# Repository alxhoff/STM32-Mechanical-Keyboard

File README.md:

# HID Keyboard - rebooted, stay tuned

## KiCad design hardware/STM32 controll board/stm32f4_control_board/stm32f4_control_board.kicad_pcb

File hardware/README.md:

# mech-keyboard-hardware
Hardware to accompany the stm32 firmware. Test board is based around a Nucleo144

## Status

Test keypads have been fabricated and tested working, test keyboard is in final stages of design.

## Images

https://photos.app.goo.gl/a2BMehDUMZQ9xBT23
https://photos.app.goo.gl/sn7a3JNhBGbZmrqK2

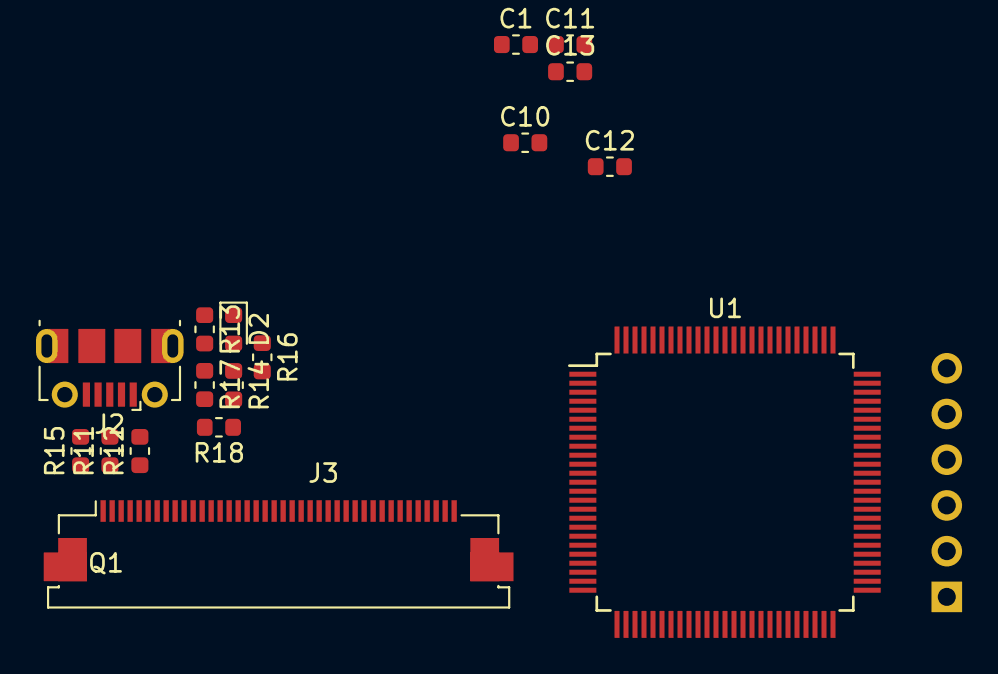
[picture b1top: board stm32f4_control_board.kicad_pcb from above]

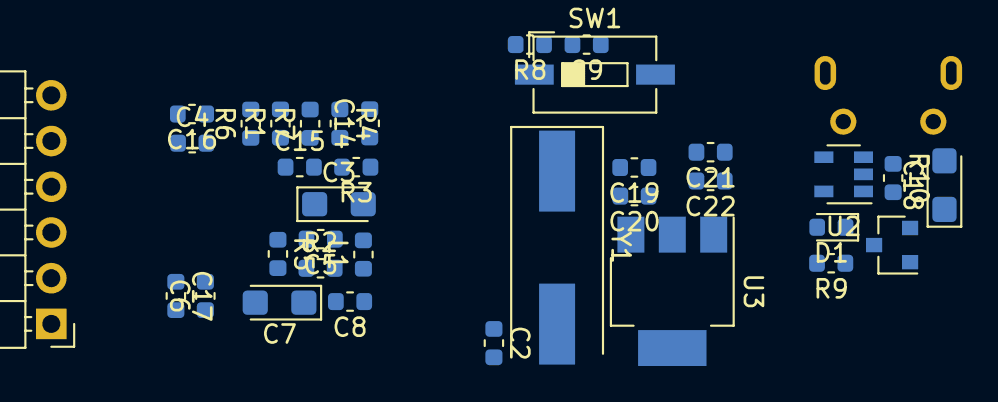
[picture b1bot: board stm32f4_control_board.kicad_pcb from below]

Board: 2 copper layers, 52 parts (35 on the bottom side), 54 nets, no tracks yet.

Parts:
C1, C2: 20pF; C_0603_1608Metric
C3, C7, C18: 1uF; CP_EIA-3216-18_Kemet-A
C4, C6: 2.2uF; C_0603_1608Metric
C5, C8, C9, C10, C11, C12, C13, C14, C15, C16, C17, C20, C22: 100nF; C_0603_1608Metric
C19, C21: 1uF; C_0603_1608Metric
D1: Green; D_0603_1608Metric
D2: Red; D_0603_1608Metric
J1: Conn_01x06_Female; PinHeader_1x06_P2.54mm_Horizontal
J2: USB_B_Micro; USB_Micro-B_Molex-105017-0001
J3: Conn_01x26_Female; Molex_54132-5033_1x40-1MP_P0.5mm_Horizontal
L1: L_Small; L_0603_1608Metric
Q1: 9013; SOT-23
R1: 510; R_0603_1608Metric
R2: 47; R_0603_1608Metric
R3, R4, R15, R17: 0; R_0603_1608Metric
R5, R8, R18: 10K; R_0603_1608Metric
R6, R7: 4K7; R_0603_1608Metric
R9: 330; R_0603_1608Metric
R10, R13, R14, R16: 47K; R_0603_1608Metric
R11, R12: 22; R_0603_1608Metric
SW1: SW_Push; SW_DIP_SPSTx01_Slide_6.7x4.1mm_W6.73mm_P2.54mm_LowProfile_J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
U1: STM32F407VGTx; LQFP-100_14x14mm_P0.5mm
U2: STMPS2141; SOT-23-5
U3: AMS1117-3.3; SOT-223-3_TabPin2
Y1: 8MHz; Crystal_SMD_HC49-SD

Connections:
+3V3: C21.2, C22.2, J3.26, R9.1, R14.2, R16.2, R18.1, U3.2
+5V: C19.2, C20.2, J3.1, J3.25, U2.5, U3.3
GPIO2: J3.3, U1.16
GPIO3: J3.4, U1.17
GPIO4: J3.5, U1.18
GPIO5: J3.6, U1.1
GPIO6: J3.7, U1.2
GPIO7: J3.8, U1.3
GPIO8: J3.9, U1.4
GPIO9: J3.10, U1.5
GPIO10: J3.11, U1.23
GPIO11: J3.12, U1.24
GPIO12: J3.13, U1.29
I2C3_SCL: J3.18, U1.67
I2C3_SDA: J3.17, U1.66
MCO: C1.2, J1.1, U1.12, Y1.1
NRST: C9.2, J1.3, R8.1, SW1.1, U1.14
unnamed: C2.2, U1.13, Y1.2
unnamed: C4.1, U1.73
unnamed: C6.1, U1.49
unnamed: D1.1, Q1.3
unnamed: D1.2, R9.2
unnamed: D2.1, R13.2, R16.1, U2.3
unnamed: D2.2, R14.1
unnamed: J2.2, R12.2
unnamed: J2.3, R11.2
unnamed: J2.4, R15.2
unnamed: Q1.2, R10.2
unnamed: R1.2, U1.94
unnamed: R2.2, U1.21
unnamed: R3.1, U1.6
unnamed: R4.1, U1.99
unnamed: R5.2, U1.37
unnamed: R17.1, U2.4
OTF_GS_overcurrent: R13.1, U1.86
PB6-I2C1_SCL: J3.22, U1.92
PB9-I2C1_SDA: J3.23, U1.96
PC0: R17.2, R18.2, U1.15
SPI_MISO: J3.20, U1.31
SPI_MOSI: J3.19, U1.32
SPI_SCK: J3.21, U1.30
SWCLK: J1.5, U1.76
SWDIO: J1.4, U1.72
SWO: J1.6, U1.89
UART2_CK: J3.16, U1.88
UART2_RX: J3.15, U1.26
UART2_TX: J3.14, U1.25
USB_OTG_DM: R12.1, U1.70
USB_OTG_DP: R11.1, U1.71
USB_OTG_GND: C1.1, C2.1, C3.2, C4.2, C5.1, C6.2, C7.2, C8.1, C9.1, C10.1, C11.1, C12.1, C13.1, C14.1, C15.1, C16.1, C17.1, C18.2, C19.1, C20.1, C21.1, C22.1, J1.2, J2.5, J2.6, J3.2, J3.24, Q1.1, R1.1, R4.2, SW1.2, U1.10, U1.20, U1.27, U1.74, U2.2, U3.1
USB_OTG_ID: R15.1, U1.69
USB_OTG_VBUS: C18.1, J2.1, R10.1, U1.68, U2.1
VDD: C10.2, C11.2, C12.2, C13.2, C14.2, C15.2, C16.2, C17.2, L1.2, R3.2, R5.1, R6.1, R7.1, R8.2, U1.11, U1.19, U1.28, U1.50, U1.75, U1.100
VDDA: C3.1, C5.2, C7.1, C8.2, L1.1, R2.1, U1.22

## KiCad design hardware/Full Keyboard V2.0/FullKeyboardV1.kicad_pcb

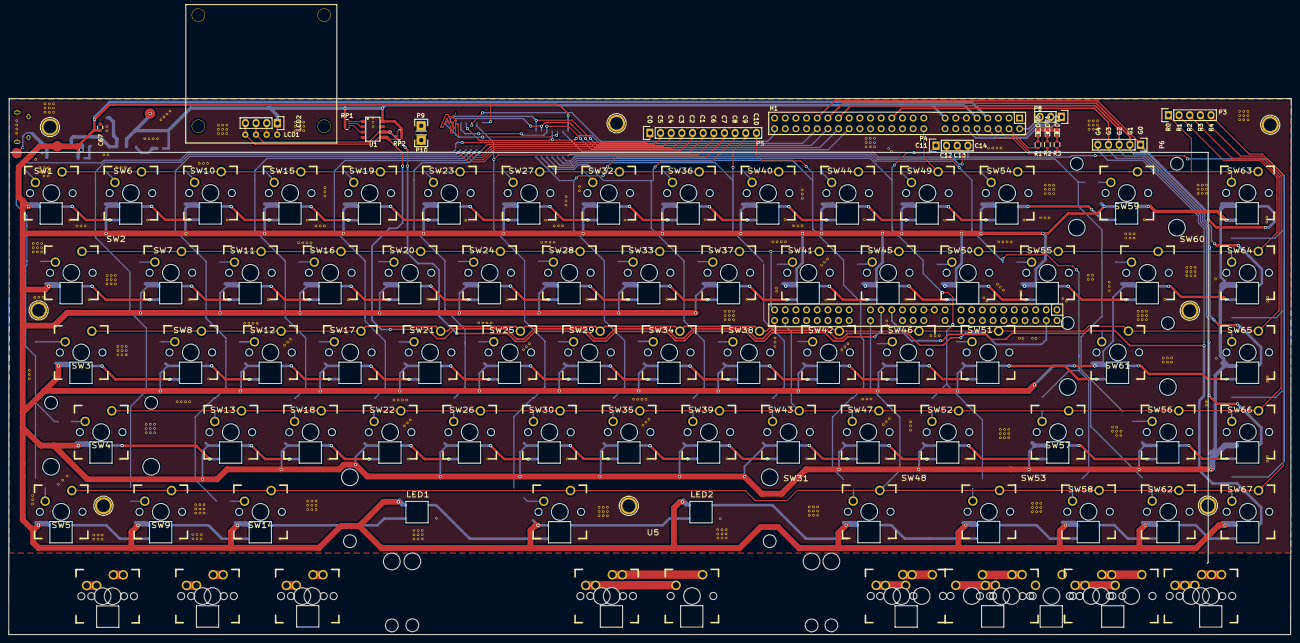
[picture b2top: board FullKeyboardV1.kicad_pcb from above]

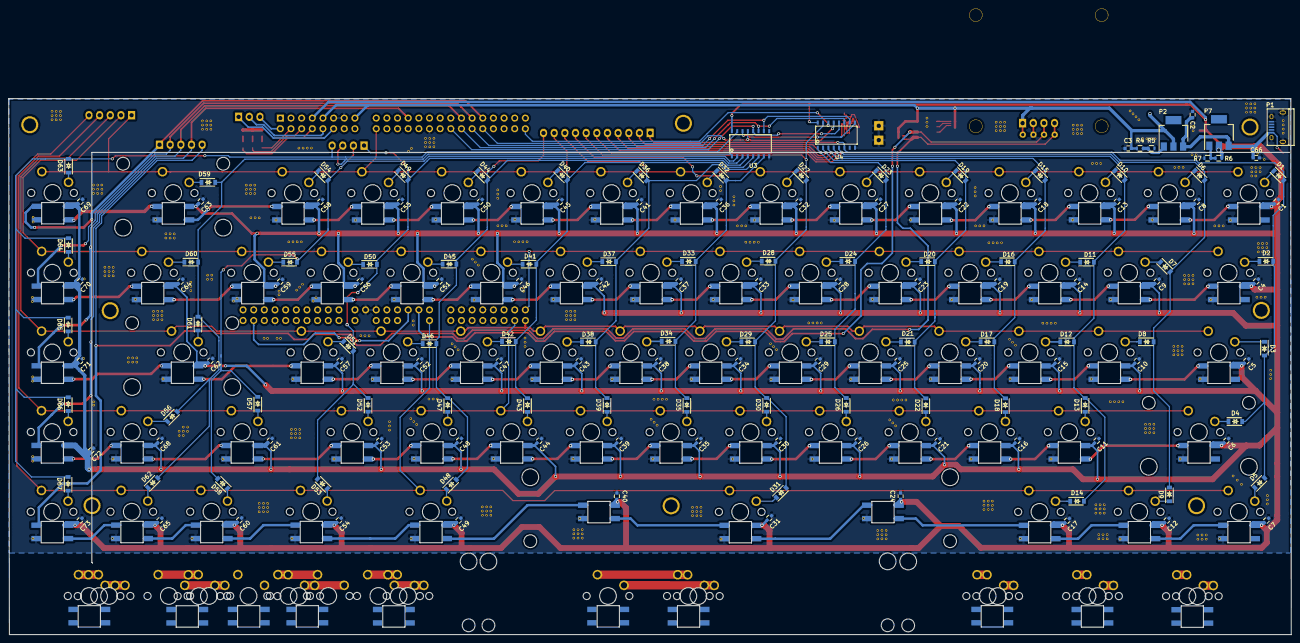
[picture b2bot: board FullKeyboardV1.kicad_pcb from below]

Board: 2 copper layers, 305.8 x 127.8 mm, 242 parts (148 on the bottom side), 182 nets.

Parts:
C1, C4, C5, C6, C7, C8, C9, C10, C11, C12, C13, C14, C15, C16, C17, C18, C19, C20, C21, C22, C23, C24, C25, C26, C27, C28, C29, C30, C31, C32, C33, C34, C35, C36, C37, C38, C39, C40, C41, C42, C43, C44, C45, C46, C47, C48, C49, C50, C51, C52, C53, C54, C55, C56, C57, C58, C59, C60, C61, C62, C63, C64, C65, C68, C69, C70, C71, C72, C73: C_Small; C_0603
C2, C66: C; C_0603
C3, C67: CP1; C_0603
D1, D2, D3, D4, D5, D6, D7, D8, D9, D10, D11, D12, D13, D14, D15, D16, D17, D18, D19, D20, D21, D22, D23, D24, D25, D26, D27, D28, D29, D30, D31, D32, D33, D34, D35, D36, D37, D38, D39, D40, D41, D42, D43, D44, D45, D46, D47, D48, D49, D50, D51, D52, D53, D54, D55, D56, D57, D58, D59, D60, D61, D62, D63, D64, D65, D66, D67: D_Small; SOD-123
D70, D71, D72: LED; LED_0603
H1: Nucleo144_H0; Nucleo144_W28384
LCD1: 1.3_inch_LCD
LCD2: SPI_spare; Pin_Header_Straight_1x04
LED1, LED2: ws2812; RGB_WS2812_LED
P1: USB_OTG; USB_Micro-B
P2, P7: AMS1117; SOT-223
P3, P6: CONN_01X05; Pin_Header_Straight_1x05
P4: CONN_01X04; Pin_Header_Straight_1x04
P5: CONN_01X11; Pin_Header_Straight_1x11
P8: CONN_01X03; Pin_Header_Straight_1x03
P9, P10: CONN_01X01; Pin_Header_Straight_1x01
R1, R2, R3, R4, R5, R6, R7: R; R_0603
RP1, RP2: R_PACK4; R_Array_Convex_4x0402
SW1: Esc; RGB_CHERRY_1.0
SW2: Tab; RGB_CHERRY_1.5
SW3: Caps; RGB_CHERRY_1.75
SW4: LShift; RGB_CHERRY_2.25
SW5: RCtrl; RGB_CHERRY_1.25
SW6: 1; RGB_CHERRY_1.0
SW7: Q; RGB_CHERRY_1.0
SW8: A; RGB_CHERRY_1.0
SW9: RGUI; RGB_CHERRY_1.25
SW10: 2; RGB_CHERRY_1.0
SW11: W; RGB_CHERRY_1.0
SW12: S; RGB_CHERRY_1.0
SW13: Z; RGB_CHERRY_1.0
SW14: RAlt; RGB_CHERRY_1.25
SW15: 3; RGB_CHERRY_1.0
SW16: E; RGB_CHERRY_1.0
SW17: D; RGB_CHERRY_1.0
SW18: X; RGB_CHERRY_1.0
SW19: 4; RGB_CHERRY_1.0
SW20: R; RGB_CHERRY_1.0
SW21: F; RGB_CHERRY_1.0
SW22: C; RGB_CHERRY_1.0
SW23: 5; RGB_CHERRY_1.0
SW24: T; RGB_CHERRY_1.0
SW25: G; RGB_CHERRY_1.0
SW26: V; RGB_CHERRY_1.0
SW27: 6; RGB_CHERRY_1.0
SW28: Y; RGB_CHERRY_1.0
SW29: H; RGB_CHERRY_1.0
SW30: B; RGB_CHERRY_1.0
SW31: Space; RGB_CHERRY_6.25
SW32: 7; RGB_CHERRY_1.0
SW33: U; RGB_CHERRY_1.0
SW34: J; RGB_CHERRY_1.0
SW35: N; RGB_CHERRY_1.0
SW36: 8; RGB_CHERRY_1.0
SW37: I; RGB_CHERRY_1.0
SW38: K; RGB_CHERRY_1.0
SW39: M; RGB_CHERRY_1.0
SW40: 9; RGB_CHERRY_1.0
SW41: O; RGB_CHERRY_1.0
SW42: L; RGB_CHERRY_1.0
SW43: <; RGB_CHERRY_1.0
SW44: 0; RGB_CHERRY_1.0
SW45: P; RGB_CHERRY_1.0
SW46: ;; RGB_CHERRY_1.0
SW47: >; RGB_CHERRY_1.0
SW48: Func; RGB_CHERRY_1.5
SW49: Minus; RGB_CHERRY_1.0
SW50: [; RGB_CHERRY_1.0
SW51: "; RGB_CHERRY_1.0
SW52: /; RGB_CHERRY_1.0
SW53: Macro; RGB_CHERRY_1.5
SW54: =; RGB_CHERRY_1.0
SW55: ]; RGB_CHERRY_1.0
SW56: Up; RGB_CHERRY_1.0
SW57: RShift; RGB_CHERRY_1.75
SW58: Left; RGB_CHERRY_1.0
SW59: BKSPC; RGB_CHERRY_2.0
SW60: \; RGB_CHERRY_1.5
SW61: Enter; RGB_CHERRY_2.25
SW62: Down; RGB_CHERRY_1.0
SW63: Til; RGB_CHERRY_1.0
SW64: Del; RGB_CHERRY_1.0
SW65: Pg Up; RGB_CHERRY_1.0
SW66: Pg Dw; RGB_CHERRY_1.0
SW67: Right; RGB_CHERRY_1.0
T1: Vin; TestPad
T2, T3: Vout; TestPad
U1: AT24C02; MY-SOP8
U2: Logo
U3, U4: SN74HC595; SOP16
U5: Cherry_bottom_row; RGB_CHERRY_SPACEBAR_ROW

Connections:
+3V3: C1.2, C4.2, C5.2, C6.2, C7.2, C8.2, C9.2, C10.2, C11.2, C12.2, C13.2, C14.2, C15.2, C16.2, C17.2, C18.2, C19.2, C20.2, C21.2, C22.2, C23.2, C24.1, C25.2, C26.2, C27.2, C28.2, C29.2, C30.2, C31.2, C32.2, C33.2, C34.2, C35.2, C36.2, C37.2, C38.2, C39.2, C40.2, C41.2, C42.1, C43.2, C44.2, C45.2, C46.2, C47.2, C48.2, C49.2, C50.2, C51.2, C52.2, C53.2, C54.2, C55.2, C56.2, C57.2, C58.2, C59.2, C60.2, C61.2, C62.2, C63.2, C64.2, C65.2, C67.1, C68.2, C69.2, C70.2, C71.2, C72.2, C73.2, H1.7, LED1.1, LED2.1, P7.2, R6.1, SW1.3, SW2.3, SW3.3, SW4.3, SW5.3, SW6.3, SW7.3, SW8.3, SW9.3, SW10.3, SW11.3, SW12.3, SW13.3, SW14.3, SW15.3, SW16.3, SW17.3, SW18.3, SW19.3, SW20.3, SW21.3, SW22.3, SW23.3, SW24.3, SW25.3, SW26.3, SW27.3, SW28.3, SW29.3, SW30.3, SW31.3, SW32.3, SW33.3, SW34.3, SW35.3, SW36.3, SW37.3, SW38.3, SW39.3, SW40.3, SW41.3, SW42.3, SW43.3, SW44.3, SW45.3, SW46.3, SW47.3, SW48.3, SW49.3, SW50.3, SW51.3, SW52.3, SW53.3, SW54.3, SW55.3, SW56.3, SW57.3, SW58.3, SW59.3, SW60.3, SW61.3, SW62.3, SW63.3, SW64.3, SW65.3, SW66.3, SW67.3, T3.1, U3.16, U4.16
+5V: C3.1, H1.9, H1.15, LCD1.1, LCD2.1, P2.2, R4.1, RP1.1, RP1.2, RP1.3, RP1.4, RP2.1, RP2.2, RP2.3, RP2.4, T2.1, U1.8
/COL0: D1.2, D2.2, D3.2, D4.2, D5.2, P5.1, U4.6
/COL1: D6.2, D7.2, D8.2, D9.2, P5.6, U4.5
/COL2: D10.2, D11.2, D12.2, D13.2, D14.2, P5.5, U4.4
/COL3: D15.2, D16.2, D17.2, D18.2, P5.4, U4.3
/COL4: D19.2, D20.2, D21.2, D22.2, P5.3, U4.2
/COL5: D23.2, D24.2, D25.2, D26.2, P5.2, U4.1
/COL6: D27.2, D28.2, D29.2, D30.2, D31.2, P5.7, U4.15
/COL7: D32.2, D33.2, D34.2, D35.2, P5.8, U3.7
/COL8: D36.2, D37.2, D38.2, D39.2, P5.9, U3.6
/COL9: D40.2, D41.2, D42.2, D43.2, P5.10, U3.5
/COL10: D44.2, D45.2, D46.2, D47.2, D48.2, P5.11, U3.4
/COL11: D49.2, D50.2, D51.2, D52.2, D53.2, P4.1, U3.3
/COL12: D54.2, D55.2, D57.2, D58.2, P4.2, U3.2
/COL13: D56.2, D59.2, D60.2, D61.2, D62.2, P4.3, U3.1
/COL14: D63.2, D64.2, D65.2, D66.2, D67.2, P4.4, U3.15
/LED0: H1.8, R3.1
/LED1: H1.6, R2.1
/LED2: H1.4, R1.1
/MicroSheet/OUTEN: H1.38, U3.13, U4.13
/MicroSheet/RCLK: H1.32, U3.12, U4.12
/MicroSheet/SD_CLK: H1.10, P8.2
/MicroSheet/SD_CMD: H1.12, P8.1
/MicroSheet/SD_DO: H1.2, P8.3
/MicroSheet/SER_IN: H1.46, U4.14
/MicroSheet/SRCLK: H1.34, U3.11, U4.11
/MicroSheet/SRCLR: H1.36, U3.10, U4.10
/RGB0: H1.37, P6.1, SW63.6
/RGB1: H1.35, P6.2, SW64.6
/RGB2: H1.33, P6.3, SW65.6
/RGB3: H1.23, P6.4, SW66.6
/RGB4: H1.77, P6.5, SW67.6
/ROW0: H1.18, P3.1, SW1.1, SW6.1, SW10.1, SW15.1, SW19.1, SW23.1, SW27.1, SW32.1, SW36.1, SW40.1, SW44.1, SW49.1, SW54.1, SW59.1, SW63.1
/ROW1: H1.99, P3.2, SW2.1, SW7.1, SW11.1, SW16.1, SW20.1, SW24.1, SW28.1, SW33.1, SW37.1, SW41.1, SW45.1, SW50.1, SW55.1, SW60.1, SW64.1
/ROW2: H1.100, P3.3, SW3.1, SW8.1, SW12.1, SW17.1, SW21.1, SW25.1, SW29.1, SW34.1, SW38.1, SW42.1, SW46.1, SW51.1, SW61.1, SW65.1
/ROW3: H1.98, P3.4, SW4.1, SW13.1, SW18.1, SW22.1, SW26.1, SW30.1, SW35.1, SW39.1, SW43.1, SW47.1, SW52.1, SW56.1, SW57.1, SW66.1
/ROW4: H1.82, P3.5, SW5.1, SW9.1, SW14.1, SW31.1, SW48.1, SW53.1, SW58.1, SW62.1, SW67.1
GND: C1.1, C2.2, C3.2, C4.1, C5.1, C6.1, C7.1, C8.1, C9.1, C10.1, C11.1, C12.1, C13.1, C14.1, C15.1, C16.1, C17.1, C18.1, C19.1, C20.1, C21.1, C22.1, C23.1, C24.2, C25.1, C26.1, C27.1, C28.1, C29.1, C30.1, C31.1, C32.1, C33.1, C34.1, C35.1, C36.1, C37.1, C38.1, C39.1, C40.1, C41.1, C42.2, C43.1, C44.1, C45.1, C46.1, C47.1, C48.1, C49.1, C50.1, C51.1, C52.1, C53.1, C54.1, C55.1, C56.1, C57.1, C58.1, C59.1, C60.1, C61.1, C62.1, C63.1, C64.1, C65.1, C66.2, C67.2, C68.1, C69.1, C70.1, C71.1, C72.1, C73.1, D70.1, D71.1, D72.1, H1.11, H1.13, H1.28, H1.54, H1.69, H1.71, LCD1.2, LCD2.2, LED1.3, LED2.3, P1.5, P1.6, P9.1, P10.1, R5.2, R7.2, SW1.5, SW2.5, SW3.5, SW4.5, SW5.5, SW6.5, SW7.5, SW8.5, SW9.5, SW10.5, SW11.5, SW12.5, SW13.5, SW14.5, SW15.5, SW16.5, SW17.5, SW18.5, SW19.5, SW20.5, SW21.5, SW22.5, SW23.5, SW24.5, SW25.5, SW26.5, SW27.5, SW28.5, SW29.5, SW30.5, SW31.5, SW32.5, SW33.5, SW34.5, SW35.5, SW36.5, SW37.5, SW38.5, SW39.5, SW40.5, SW41.5, SW42.5, SW43.5, SW44.5, SW45.5, SW46.5, SW47.5, SW48.5, SW49.5, SW50.5, SW51.5, SW52.5, SW53.5, SW54.5, SW55.5, SW56.5, SW57.5, SW58.5, SW59.5, SW60.5, SW61.5, SW62.5, SW63.5, SW64.5, SW65.5, SW66.5, SW67.5, U1.4, U1.7, U3.8, U4.8
unnamed: C2.1, C66.1, P1.1, P2.3, P7.3, T1.1
unnamed: D1.1, SW1.2
unnamed: D2.1, SW2.2
unnamed: D3.1, SW3.2
unnamed: D4.1, SW4.2
unnamed: D5.1, SW5.2
unnamed: D6.1, SW6.2
unnamed: D7.1, SW7.2
unnamed: D8.1, SW8.2
unnamed: D9.1, SW9.2
unnamed: D10.1, SW10.2
unnamed: D11.1, SW11.2
unnamed: D12.1, SW12.2
unnamed: D13.1, SW13.2
unnamed: D14.1, SW14.2
unnamed: D15.1, SW15.2
unnamed: D16.1, SW16.2
unnamed: D17.1, SW17.2
unnamed: D18.1, SW18.2
unnamed: D19.1, SW19.2
unnamed: D20.1, SW20.2
unnamed: D21.1, SW21.2
unnamed: D22.1, SW22.2
unnamed: D23.1, SW23.2
unnamed: D24.1, SW24.2
unnamed: D25.1, SW25.2
unnamed: D26.1, SW26.2
unnamed: D27.1, SW27.2
unnamed: D28.1, SW28.2
unnamed: D29.1, SW29.2
unnamed: D30.1, SW30.2
unnamed: D31.1, SW31.2
unnamed: D32.1, SW32.2
unnamed: D33.1, SW33.2
unnamed: D34.1, SW34.2
unnamed: D35.1, SW35.2
unnamed: D36.1, SW36.2
unnamed: D37.1, SW37.2
unnamed: D38.1, SW38.2
unnamed: D39.1, SW39.2
unnamed: D40.1, SW40.2
unnamed: D41.1, SW41.2
unnamed: D42.1, SW42.2
unnamed: D43.1, SW43.2
unnamed: D44.1, SW44.2
unnamed: D45.1, SW45.2
unnamed: D46.1, SW46.2
unnamed: D47.1, SW47.2
unnamed: D48.1, SW48.2
unnamed: D49.1, SW49.2
unnamed: D50.1, SW50.2
unnamed: D51.1, SW51.2
unnamed: D52.1, SW52.2
unnamed: D53.1, SW53.2
unnamed: D54.1, SW54.2
unnamed: D55.1, SW55.2
unnamed: D56.1, SW56.2
unnamed: D57.1, SW57.2
unnamed: D58.1, SW58.2
unnamed: D59.1, SW59.2
unnamed: D60.1, SW60.2
unnamed: D61.1, SW61.2
unnamed: D62.1, SW62.2
unnamed: D63.1, SW63.2
unnamed: D64.1, SW64.2
unnamed: D65.1, SW65.2
unnamed: D66.1, SW66.2
unnamed: D67.1, SW67.2
unnamed: D70.2, R1.2
unnamed: D71.2, R2.2
unnamed: D72.2, R3.2
unnamed: LED1.2, SW14.6
unnamed: LED1.4, SW31.4
unnamed: LED2.2, SW31.6
unnamed: LED2.4, SW48.4
unnamed: P2.1, R4.2, R5.1
unnamed: P7.1, R6.2, R7.1
unnamed: RP1.6, U1.3
unnamed: RP1.7, U1.2
unnamed: RP1.8, U1.1
unnamed: SW1.6, SW6.4
unnamed: SW2.6, SW7.4
unnamed: SW3.6, SW8.4
unnamed: SW5.6, SW9.4
unnamed: SW6.6, SW10.4
unnamed: SW10.6, SW15.4
unnamed: SW7.6, SW11.4
unnamed: SW11.6, SW16.4
unnamed: SW8.6, SW12.4
unnamed: SW12.6, SW17.4
unnamed: SW4.6, SW13.4
unnamed: SW13.6, SW18.4
unnamed: SW9.6, SW14.4
unnamed: SW15.6, SW19.4
unnamed: SW16.6, SW20.4
unnamed: SW17.6, SW21.4
unnamed: SW18.6, SW22.4
unnamed: SW19.6, SW23.4
unnamed: SW20.6, SW24.4
unnamed: SW21.6, SW25.4
unnamed: SW22.6, SW26.4
unnamed: SW23.6, SW27.4
unnamed: SW24.6, SW28.4
unnamed: SW25.6, SW29.4
unnamed: SW26.6, SW30.4
unnamed: SW27.6, SW32.4
unnamed: SW28.6, SW33.4
unnamed: SW29.6, SW34.4
unnamed: SW30.6, SW35.4
unnamed: SW32.6, SW36.4
unnamed: SW33.6, SW37.4
unnamed: SW34.6, SW38.4
unnamed: SW35.6, SW39.4
unnamed: SW36.6, SW40.4
unnamed: SW37.6, SW41.4
unnamed: SW38.6, SW42.4
unnamed: SW39.6, SW43.4
unnamed: SW40.6, SW44.4
unnamed: SW41.6, SW45.4
unnamed: SW42.6, SW46.4
unnamed: SW43.6, SW47.4
unnamed: SW44.6, SW49.4
unnamed: SW45.6, SW50.4
unnamed: SW46.6, SW51.4
unnamed: SW47.6, SW52.4
unnamed: SW48.6, SW53.4
unnamed: SW49.6, SW54.4
unnamed: SW50.6, SW55.4
unnamed: SW51.6, SW61.4
unnamed: SW52.6, SW57.4
unnamed: SW53.6, SW58.4
unnamed: SW54.6, SW59.4
unnamed: SW55.6, SW60.4
unnamed: SW56.4, SW57.6
unnamed: SW56.6, SW66.4
unnamed: SW58.6, SW62.4
unnamed: SW59.6, SW63.4
unnamed: SW60.6, SW64.4
unnamed: SW61.6, SW65.4
unnamed: SW62.6, SW67.4
unnamed: U3.14, U4.9
SCL: H1.79, LCD1.3, LCD2.3, RP2.7, U1.6
SDA: H1.50, LCD1.4, LCD2.4, RP2.8, U1.5

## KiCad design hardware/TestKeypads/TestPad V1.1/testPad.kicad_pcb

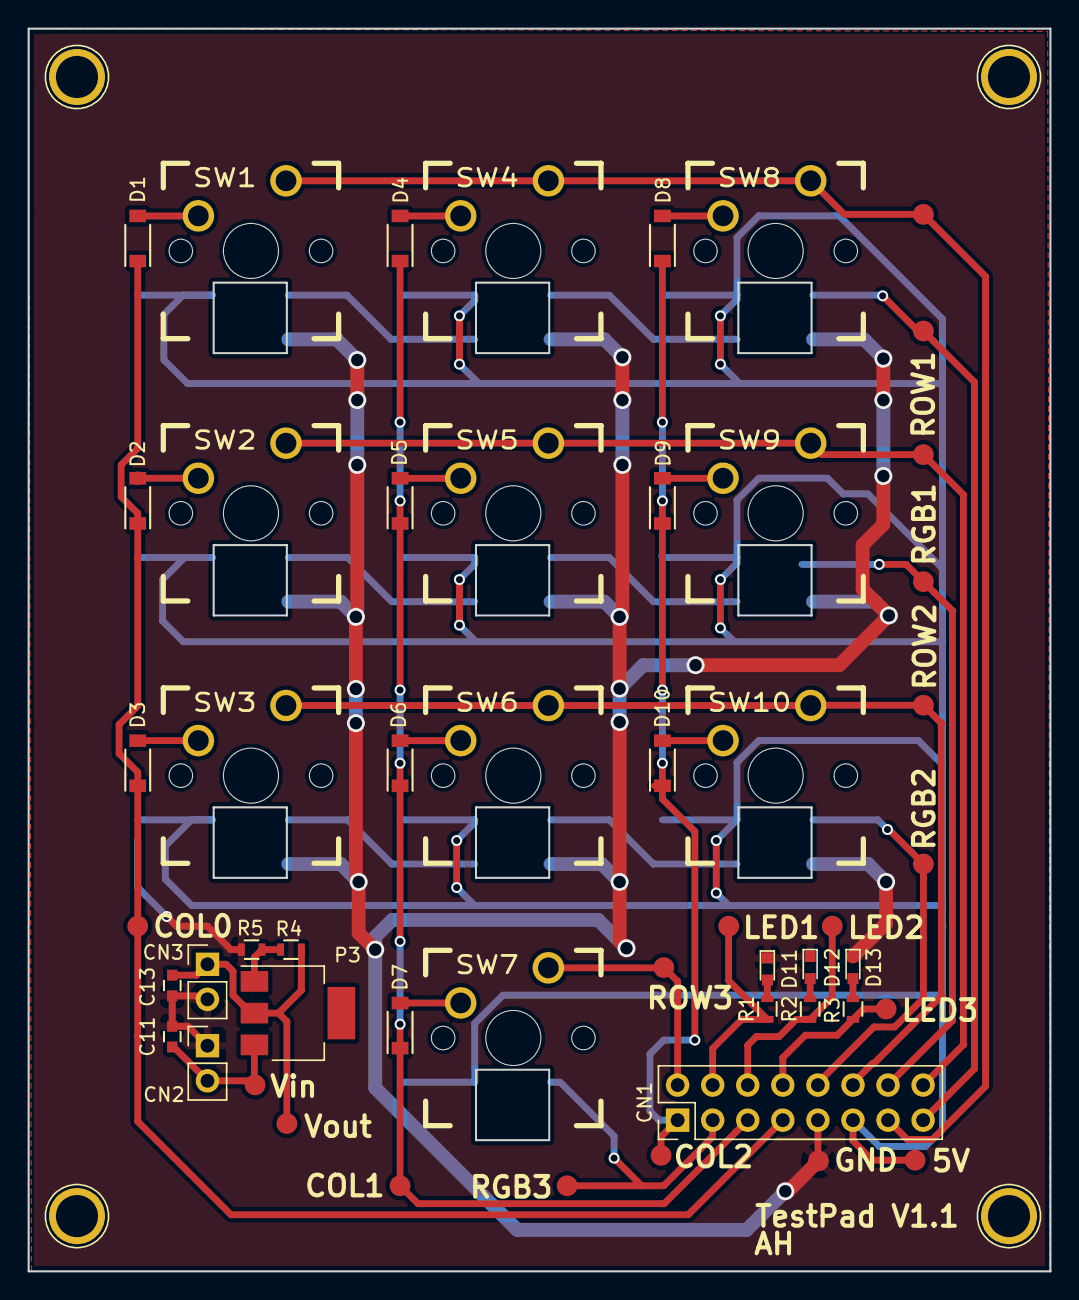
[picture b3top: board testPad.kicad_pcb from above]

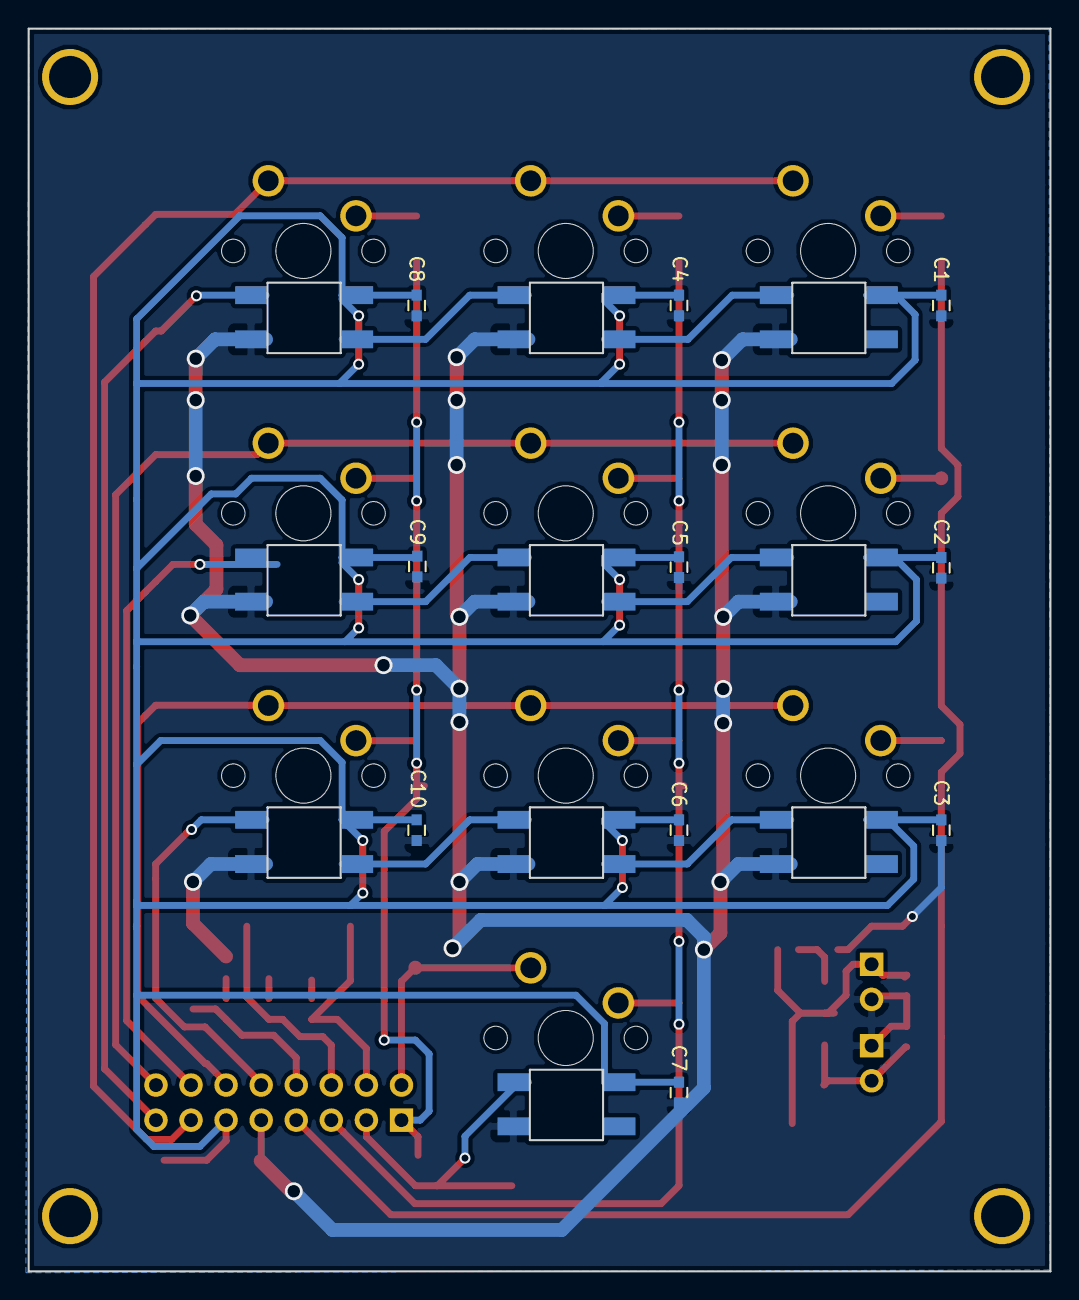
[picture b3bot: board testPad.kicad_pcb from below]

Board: 2 copper layers, 74.0 x 90.0 mm, 62 parts (10 on the bottom side), 38 nets.

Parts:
C1, C2, C3, C4, C5, C6, C7, C8, C9, C10, C11: C; C_0603
C13: CP1; C_0603
CN1: CONN_02X08; Pin_Header_Straight_2x08_Pitch2.54mm
CN2, CN3: CONN_01X02; Pin_Header_Straight_1x02_Pitch2.54mm
D1, D2, D3, D4, D5, D6, D7, D8, D9, D10: D; SOD-123
D11, D12, D13: LED; LED_0603
P3: AMS1117; SOT-223
R1, R2, R3, R4, R5: R; R_0603
SW1, SW2, SW3, SW4, SW5, SW6, SW7, SW8, SW9, SW10: RGB_FUCKIN_WORK_POS_KICAD; RGB_CHERRY_1.0
TP1, TP2, TP3, TP4, TP5, TP6, TP7, TP8, TP9, TP10, TP11, TP12, TP13, TP14, TP15, TP16, TP17, TP18: TEST; testpad_small

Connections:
+5V: C1.2, C2.2, C3.2, C4.2, C5.2, C6.2, C7.2, C8.2, C9.2, C10.2, CN1.11, SW1.3, SW2.3, SW3.3, SW4.3, SW5.3, SW6.3, SW7.3, SW8.3, SW9.3, SW10.3, TP16.1
/COL0: CN1.7, SW1.1, SW4.1, SW8.1, TP1.1
/COL1: CN1.5, SW2.1, SW5.1, SW9.1, TP2.1
/COL2: CN1.1, SW3.1, SW6.1, SW10.1, TP3.1
/COL3: SW7.1, TP4.1
/LED0: CN1.4, R1.1, TP12.1
/LED1: CN1.6, R2.1, TP13.1
/LED2: CN1.8, R3.1, TP14.1
/RGB0: CN1.15, SW8.6, TP8.1
/RGB1: CN1.14, SW9.6, TP9.1
/RGB2: CN1.10, SW10.6, TP10.1
/RGB3: CN1.3, SW7.6, TP11.1
/ROW0: CN1.13, D1.1, D2.1, D3.1, TP5.1
/ROW1: CN1.16, D4.1, D5.1, D6.1, D7.1, TP6.1
/ROW2: CN1.12, D8.1, D9.1, D10.1, TP7.1
GND: C1.1, C2.1, C3.1, C4.1, C5.1, C6.1, C7.1, C8.1, C9.1, C10.1, C11.2, C13.2, CN1.9, CN2.1, CN3.2, D11.1, D12.1, D13.1, R5.2, SW1.5, SW2.5, SW3.5, SW4.5, SW5.5, SW6.5, SW7.5, SW8.5, SW9.5, SW10.5, TP15.1
unnamed: C11.1, CN2.2, P3.3, TP17.1
unnamed: C13.1, CN3.1, P3.2, R4.1, TP18.1
unnamed: D1.2, SW1.2
unnamed: D2.2, SW2.2
unnamed: D3.2, SW3.2
unnamed: D4.2, SW4.2
unnamed: D5.2, SW5.2
unnamed: D6.2, SW6.2
unnamed: D7.2, SW7.2
unnamed: D8.2, SW8.2
unnamed: D9.2, SW9.2
unnamed: D10.2, SW10.2
unnamed: D11.2, R1.2
unnamed: D12.2, R2.2
unnamed: D13.2, R3.2
unnamed: P3.1, R4.2, R5.1
unnamed: SW1.6, SW4.4
unnamed: SW2.6, SW5.4
unnamed: SW3.6, SW6.4
unnamed: SW4.6, SW8.4
unnamed: SW5.6, SW9.4
unnamed: SW6.6, SW10.4

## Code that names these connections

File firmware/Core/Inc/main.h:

/* USER CODE BEGIN Header */
/**
 ******************************************************************************
 * @file           : main.h
 * @brief          : Header for main.c file.
 *                   This file contains the common defines of the application.
 ******************************************************************************
 * @attention
 *
 * Copyright (c) 2022 STMicroelectronics.
 * All rights reserved.
 *
 * This software is licensed under terms that can be found in the LICENSE file
 * in the root directory of this software component.
 * If no LICENSE file comes with this software, it is provided AS-IS.
 *
 ******************************************************************************
 */
/* USER CODE END Header */

/* Define to prevent recursive inclusion -------------------------------------*/
#ifndef __MAIN_H
#define __MAIN_H

#ifdef __cplusplus
extern "C" {
#endif

/* Includes ------------------------------------------------------------------*/
#include "stm32f4xx_hal.h"

/* Private includes ----------------------------------------------------------*/
/* USER CODE BEGIN Includes */

/* USER CODE END Includes */

/* Exported types ------------------------------------------------------------*/
/* USER CODE BEGIN ET */

/* USER CODE END ET */

/* Exported constants --------------------------------------------------------*/
/* USER CODE BEGIN EC */

/* USER CODE END EC */

/* Exported macro ------------------------------------------------------------*/
/* USER CODE BEGIN EM */

/* USER CODE END EM */

void HAL_TIM_MspPostInit(TIM_HandleTypeDef *htim);

/* Exported functions prototypes ---------------------------------------------*/
void Error_Handler(void);

/* USER CODE BEGIN EFP */

/* USER CODE END EFP */

/* Private defines -----------------------------------------------------------*/
#define COL0_Pin GPIO_PIN_3
#define COL0_GPIO_Port GPIOE
#define COL1_Pin GPIO_PIN_4
#define COL1_GPIO_Port GPIOE
#define COL2_Pin GPIO_PIN_5
#define COL2_GPIO_Port GPIOE
#define COL3_Pin GPIO_PIN_6
#define COL3_GPIO_Port GPIOE
#define USER_Btn_Pin GPIO_PIN_13
#define USER_Btn_GPIO_Port GPIOC
#define BOOT_SWITCH_Pin GPIO_PIN_8
#define BOOT_SWITCH_GPIO_Port GPIOF
#define MCO_Pin GPIO_PIN_0
#define MCO_GPIO_Port GPIOH
#define RMII_MDC_Pin GPIO_PIN_1
#define RMII_MDC_GPIO_Port GPIOC
#define RMII_MDIO_Pin GPIO_PIN_2
#define RMII_MDIO_GPIO_Port GPIOA
#define RMII_RXD0_Pin GPIO_PIN_4
#define RMII_RXD0_GPIO_Port GPIOC
#define RMII_RXD1_Pin GPIO_PIN_5
#define RMII_RXD1_GPIO_Port GPIOC
#define ROW0_Pin GPIO_PIN_10
#define ROW0_GPIO_Port GPIOE
#define ROW1_Pin GPIO_PIN_12
#define ROW1_GPIO_Port GPIOE
#define ROW2_Pin GPIO_PIN_14
#define ROW2_GPIO_Port GPIOE
#define ROW3_Pin GPIO_PIN_15
#define ROW3_GPIO_Port GPIOE
#define RMII_TXD1_Pin GPIO_PIN_13
#define RMII_TXD1_GPIO_Port GPIOB
#define LD3_Pin GPIO_PIN_14
#define LD3_GPIO_Port GPIOB
#define STLK_RX_Pin GPIO_PIN_8
#define STLK_RX_GPIO_Port GPIOD
#define STLK_TX_Pin GPIO_PIN_9
#define STLK_TX_GPIO_Port GPIOD
#define USB_PowerSwitchOn_Pin GPIO_PIN_6
#define USB_PowerSwitchOn_GPIO_Port GPIOG
#define USB_OverCurrent_Pin GPIO_PIN_7
#define USB_OverCurrent_GPIO_Port GPIOG
#define USB_SOF_Pin GPIO_PIN_8
#define USB_SOF_GPIO_Port GPIOA
#define USB_VBUS_Pin GPIO_PIN_9
#define USB_VBUS_GPIO_Port GPIOA
#define USB_ID_Pin GPIO_PIN_10
#define USB_ID_GPIO_Port GPIOA
#define USB_DM_Pin GPIO_PIN_11
#define USB_DM_GPIO_Port GPIOA
#define USB_DP_Pin GPIO_PIN_12
#define USB_DP_GPIO_Port GPIOA
#define TMS_Pin GPIO_PIN_13
#define TMS_GPIO_Port GPIOA
#define TCK_Pin GPIO_PIN_14
#define TCK_GPIO_Port GPIOA
#define RMII_TX_EN_Pin GPIO_PIN_11
#define RMII_TX_EN_GPIO_Port GPIOG
#define RMII_TXD0_Pin GPIO_PIN_13
#define RMII_TXD0_GPIO_Port GPIOG
#define LD2_Pin GPIO_PIN_7
#define LD2_GPIO_Port GPIOB
/* USER CODE BEGIN Private defines */

/* USER CODE END Private defines */

#ifdef __cplusplus
}
#endif

#endif /* __MAIN_H */

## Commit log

2017-09-01 add README
2017-09-01 moved from embedded goodness repo
2017-09-07 moved into seperate repo
2017-09-07 readding licence and readme
2017-09-07 gitignore
2017-09-07 .gitignore is now working
2017-09-07 grid copy in init fixed
2017-09-08 layer list init and append tested working after layer table additions
2017-09-08 layer list append grid copy fixed
2017-09-10 layer table init appears to be working
2017-09-10 keyboard and mouse back to working after having the layers implemented dynamically via the layer list and table. new features now in branches
2017-09-10 basic layer states added, hanging on LCD print
2017-09-10 basic layers working
2017-09-13 initial macro state functions added, lookup table added
2017-09-13 macro init and macro add added, tested working
2017-09-13 macro execution added, not tested
2017-09-14 basic macros working, repeated characters are skipped, need to fix
2017-09-14 repeating characters fixed in macros
2017-09-14 repeating character's count fixed
2017-09-14 space added to lookup table, macross now accept spaces
2017-09-14 macro clean up bug fixed
2017-09-14 some TODO's added to readme
2017-09-14 macro run state exits
2017-09-14 debounce framework added
2017-09-14 macro set state code written, needs testing
2017-09-14 macro set button input debounce working, needs reverse lookup table
2017-09-15 reverse lookup implemented, lookup table needs to be completed
2017-09-16 shift modifier functionality added to macro set input
2017-09-16 basic macro set and macro run working
2017-09-16 CubeMX SPI1 and FatFS code added, builds
2017-09-16 SC chip select gpio pin config added
2017-09-16 stumped atm, returning later
2017-09-16 Revert "basic macro set and macro run working"
    This reverts commit 5b90246707fc6f731e3624cdf65e25d9801b2381.
2017-09-16 readme updated
2017-09-16 rebased master and merged screen render to fix keypad
2017-09-16 keyboard timing adjusted
2017-09-18 shift register lib fixed
2017-09-18 shift regster flashing working
2017-09-18 shift register keyboard working
2017-09-18 shift register working, single key read needs porting
2017-09-21 almost builts after restructure, need to fix include issues
2017-09-21 builds after restructure
2017-09-21 first sweep include cleanup
2017-09-21 pre merging with stable branch
2017-09-21 init tested working until main.c:610
2017-09-22 init tested working until main.c:629
2017-09-22 warning cleanup
2017-09-22 more warning cleanup
2017-09-22 scan key shift bug fixed
2017-09-22 back to working
2017-09-22 [MACRO] single key press get fixed to work with shift register
2017-09-22 [MACRO] macro set input adapter to use shift registers
2017-09-22 ssd1306 libraries modified to work with device structure
2017-09-23 ssd1306 init changed to work with init struct
2017-09-23 ssd1306 lib works
2017-09-23 ssd1306 lib updated
2017-09-24 screen object added, needs testing and furthur functions
2017-09-24 screen object works with updating
2017-09-24 screen update flashing fixed
2017-09-24 RTOS timer configs added
2017-09-24 blink cursor timer and function added, not working yet
2017-09-24 cursor rendering
2017-09-24 cursor draws over current text statically
2017-09-24 macro init bug fix
2017-09-24 CLI input processing functions added
2017-09-24 moving cursor works
2017-09-25 screen scrolls for cursor
2017-09-25 fixed welcome message init error
2017-09-25 CLI takes caracter input
2017-09-25 CLI takes shift modifier input, seems to freeze sometimes
2017-09-25 CLI mode exits
2017-09-26 error fixes
2017-09-26 debugging again
2017-10-12 Doxygen inital generation
2017-10-12 keyboard.c/h doxy
2017-10-12 keyboard.c/h doxy finished
2017-10-13 scan documented
2017-10-19 LEDs rolled back and lib slightly modified. All working
2017-10-19 LED struct updates to use update function pointer
2017-10-19 LED cleanup
2017-10-20 dots effect added
2017-10-20 rainbow right scroll added, snappy left and right both fade in and out added
2017-10-20 LED solid white added
2017-10-20 LED off added
2017-10-20 LED solid colour added
2017-10-22 LED matrix started
2017-10-22 LED RGB Dots added
2017-10-22 LED RGB dots split into solid and fading
2017-10-22 LED rainbow down added, need to fix 2nd and 3rd row bug
2017-10-22 LED row buffer bug fixed, was a pinout problem
2017-10-22 LED count row effect added
2017-10-22 LED count direction added
2017-10-22 LED count all effect added with forward direction
2017-10-22 LED count add reverse added, buggy
2017-10-22 Matrix led efect generates rows and moves them down
2017-10-23 Matrix led efect generates mutliple rows and moves them down, buggy
2017-10-23 LED buffer inversion option added
2018-01-09 RGBs configured for nucleo on full sized board
2018-01-09 Status LEDS tested working
2018-01-10 Shift register defines added to keyboard_config
2018-01-10 Shift register pull ups added to config
2018-02-07 can toggle a bit using shifts
2018-02-08 config added for extra rows
2018-02-08 keymap macros expanded to handle 75 keys
2018-02-09 buggily typing
2018-02-09 types!
2018-02-15 some speed ups
2018-02-16 get single keypress fixed
2018-02-16 single key returning correct key
2018-02-16 layers seem to work
2019-01-21 pre-restart
2019-01-21 copied and migrated to newer firmware
2019-01-21 state machine skeleton
2019-01-21 list framework added
2019-01-22 states init added, get and set state data added
2019-01-22 old debug removed
2019-01-22 working debug config
2019-01-22 shift array made into global device
2019-01-23 keymap roughly overhauled, mouse as well
2019-01-23 keymap defaults moved to seperate config header
2019-01-23 macro stuff hacked at a bit
2019-01-23 remove macro sketchyness added
2019-01-23 builds, bulk stuff commented out
2019-01-25 keymap reworked, scan and processing of input and buffers started
2019-01-26 processing buf roughly done, builds but not tested
2019-01-26 warning fixes
2019-01-26 sc for scanned key being resolved correctly in keyboard_process_scan_buff:204
2019-01-26 fixed buffer filling with new keys
2019-01-26 clean up
2019-01-26 more clean up
2019-01-26 update gitignore
2019-01-26 gitignore updated
2019-01-26 warning fixes, structured rough sent task functions
2019-01-26 Send task added
2019-01-26 Weird config problem with startup going missing
2019-01-26 Startup folder back :/
2019-01-26 keyboard report bug fix
2019-01-26 HID report config tested working for 6 keys
2019-01-26 Sends single key, doesn't reset after sending packet yet
2019-01-26 Sends empty packet following current one. seems to deadlock
2019-01-27 State machine working for send state, needs thorough testing
2019-01-27 Optimizations in key scanning
2019-01-27 Delay between packet and empty packet now dependany on USB HHID state. Packets not getting cleared at the end
2019-01-27 Scan reworked to send empty packets att he end of each sequence. Send no longer sends empty packets specifically
2019-01-27 SSD1306 printing basic message in main
2019-01-27 basic led wave working
2019-01-27 LED effects moved to header
2019-01-29 Screen -> ssd1306 api started. Screen framebuffer being drawn on screen
2019-01-29 hardware added
2019-01-29 sending macros works
2019-01-29 Boilerplate state code added for CLI, macro run and macro set
2019-01-29 warnings
2019-01-30 Cursor stuff flickering, i'm going to bed
2019-01-31 Screen cleaned up, cursor drawing
2019-01-31 caps lock added, needs debounce
2019-01-31 Screen inversion added
2019-01-31 updated licence
2019-02-07 Started stm32 control board hardware
2019-02-08 added st-link SWD interface and USB-OTG
2019-02-09 Footprints matched
2019-02-12 PCB started for control board
2019-02-17 Ribbon connector and 3v LR
2019-02-19 Updates from nixie project
2019-02-19 Removed old project
2019-02-20 Screen return signs fixed
2019-02-24 Some ghetto toggle key debounce. needs more love
2019-02-24 CLI state creating and setting string buffer
2019-02-24 CLI getting input from scan
2019-02-24 Readme cleanup
2019-02-24 CLI appending to input line, needs to track x pos and debounce input
2019-02-25 CLI string modification functions added to handle adding char's to input buffer
2019-02-25 Screen buffer interface reworked to keep framebuffer local to the screen, interfacing with CLI modified to fit and CLI string operators fixed
2019-02-26 Screen cursor handling moving out of screen
2019-02-26 CLI input handling added, added arrows
2019-02-26 Fixed CLI string input
2019-03-02 Adding line at FB index fixed
2019-03-02 Screen updated to handle not using a cursor
2019-11-13 fixed -rdynamic and _sbrk link errors
2019-11-13 Builds
2019-11-13 Cube firmware cloning added to cmake
2020-04-11 Initial HID project files from bluepill HID
2020-04-12 Random rough rewritten files, completley untested
2020-04-12 More rewritten untested code
2020-04-12 Lookup rewritten
2020-04-16 More random rewritten code, compiles but untested. Getting there
2022-11-15 Started refactor
